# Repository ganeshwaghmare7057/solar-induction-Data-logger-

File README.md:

# solar induction (Data logger)
  Description: A temperature data logger is an electronic device specifically designed to automatically monitor and store temperature data over time in SD card. I used Arduino NANO controller. Collecting the different module like DC-DC convertor, charging module, SD card module & RTC  and 3.7v DC battery. I used I2C and SPI communication protocol.

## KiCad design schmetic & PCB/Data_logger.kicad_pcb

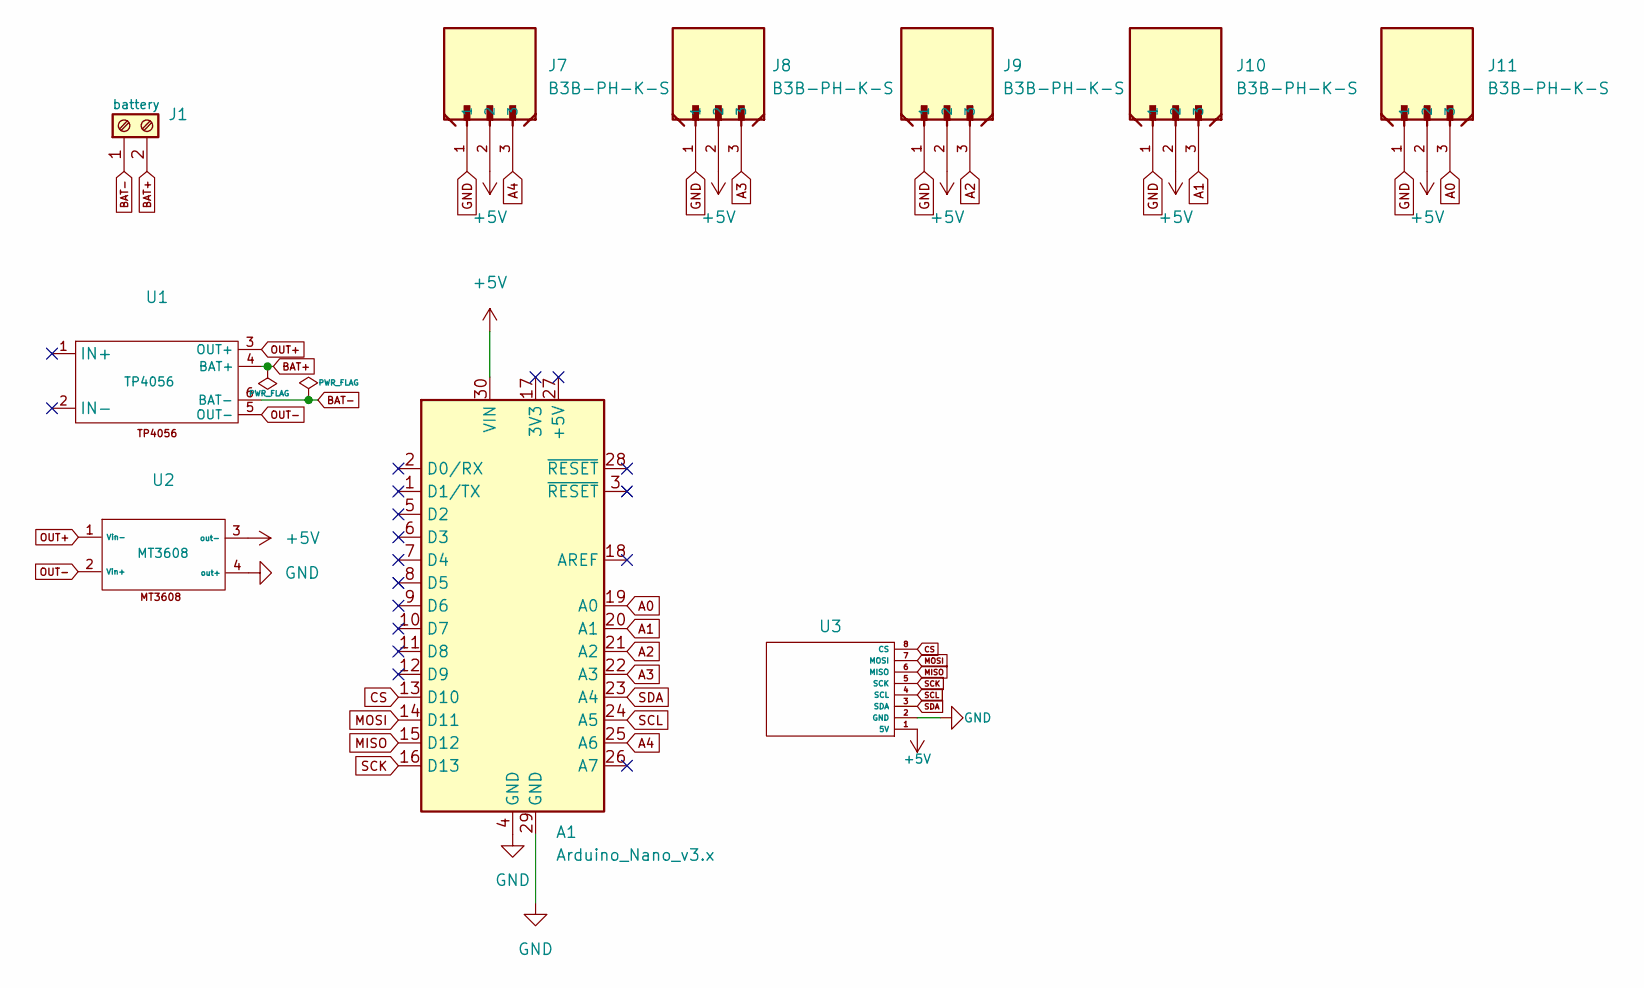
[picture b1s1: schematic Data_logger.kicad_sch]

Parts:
A1: Arduino_Nano_v3.x; Arduino_Nano
J1: battery; TerminalBlock_bornier-2_P5.08mm
J7, J8, J9, J10, J11: B3B-PH-K-S; JST_EH_B3B-EH-A_1x03_P2.50mm_Vertical
U1: TP4056
U2: MT3608
U3: SD card module

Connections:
+5V: A1.30 (VIN), J7.2, J8.2, J9.2, J10.2, J11.2, U2.3 (out+), U3.1 (5V)
A0: A1.19 (A0), J11.3
A1: A1.20 (A1), J10.3
A2: A1.21 (A2), J9.3
A3: A1.22 (A3), J8.3
A4: A1.25 (A6), J7.3
BAT+: J1.2, U1.4 (BAT+)
BAT-: J1.1, U1.6 (BAT-)
CS: A1.13 (D10), U3.8 (CS)
GND: A1.4 (GND), A1.29 (GND), J7.1, J8.1, J9.1, J10.1, J11.1, U2.4 (out-), U3.2 (GND)
MISO: A1.15 (D12), U3.6 (MISO)
MOSI: A1.14 (D11), U3.7 (MOSI)
OUT+: U1.3 (OUT+), U2.1 (Vin+)
OUT-: U1.5 (OUT-), U2.2 (Vin-)
SCK: A1.16 (D13), U3.5 (SCK)
SCL: A1.24 (A5), U3.4 (SCL)
SDA: A1.23 (A4), U3.3 (SDA)

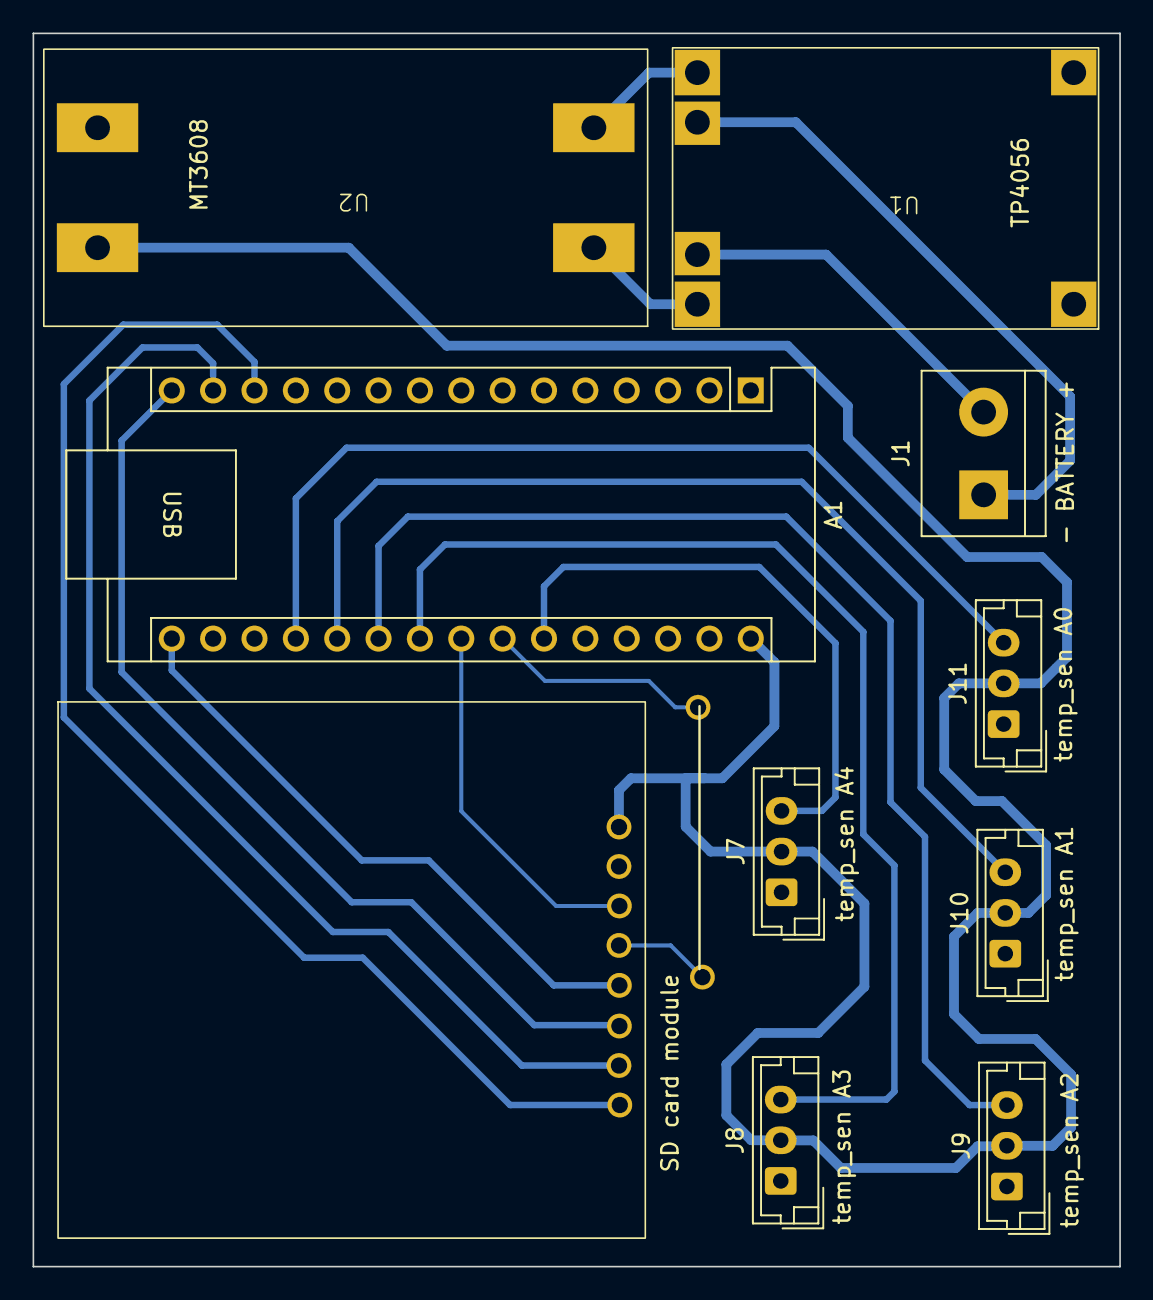
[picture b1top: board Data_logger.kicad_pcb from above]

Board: 2 copper layers, 66.7 x 75.7 mm, 10 parts (0 on the bottom side), 17 nets.
